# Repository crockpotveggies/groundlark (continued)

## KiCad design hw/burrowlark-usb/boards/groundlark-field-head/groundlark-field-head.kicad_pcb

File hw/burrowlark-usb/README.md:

# Burrowlark USB — DAQUSB-01

Burrowlark is the separate 70 × 45 mm USB-C magnetometer and enclosure-climate
sensor head. It uses the PNI 14190 RM3100 XYZ module; U3/C5 and their pressure-sensor
branches are removed. The DLVR pressure sensor is on DAQHAT-01. Prototype
[USB-head firmware](../../sw/field-head/README.md) has native and ARM checks;
physical qualification remains pending.

Native PCB render with the Groundlark favicon, Burrowlark name and
`DAQUSB-01 / REV A2` front silkscreen. The existing A2 board revision is retained.
Module, fuse and SHT45 bodies are simplified envelopes; see
[render provenance](boards/groundlark-field-head/render-provenance.json).

- [Electrical source](elec/field_head.ato)
- [Placement inputs](layout/placement.json)
- [Routed KiCad project](boards/groundlark-field-head/groundlark-field-head.kicad_pro)
- [Assembly and interface guide](../../docs/usb-sensor-head.md)
- [Firmware directory](../../sw/field-head/)

Build target: `field_head` in [hw/ato.yaml](../ato.yaml). Existing CAD filenames
and the DAQUSB-01 model identifier are preserved.

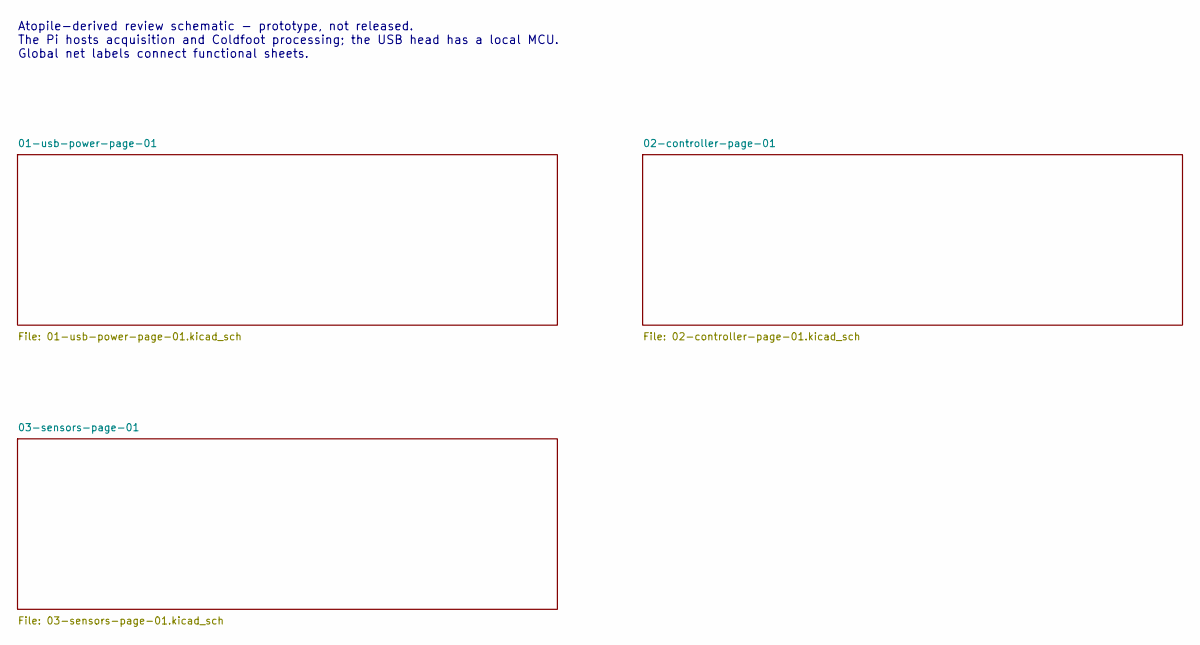
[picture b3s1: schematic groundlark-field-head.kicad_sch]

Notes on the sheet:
Atopile-derived review schematic - prototype, not released. The Pi hosts acquisition and Coldfoot processing; the USB head has a local MCU. Global net labels connect functional sheets.

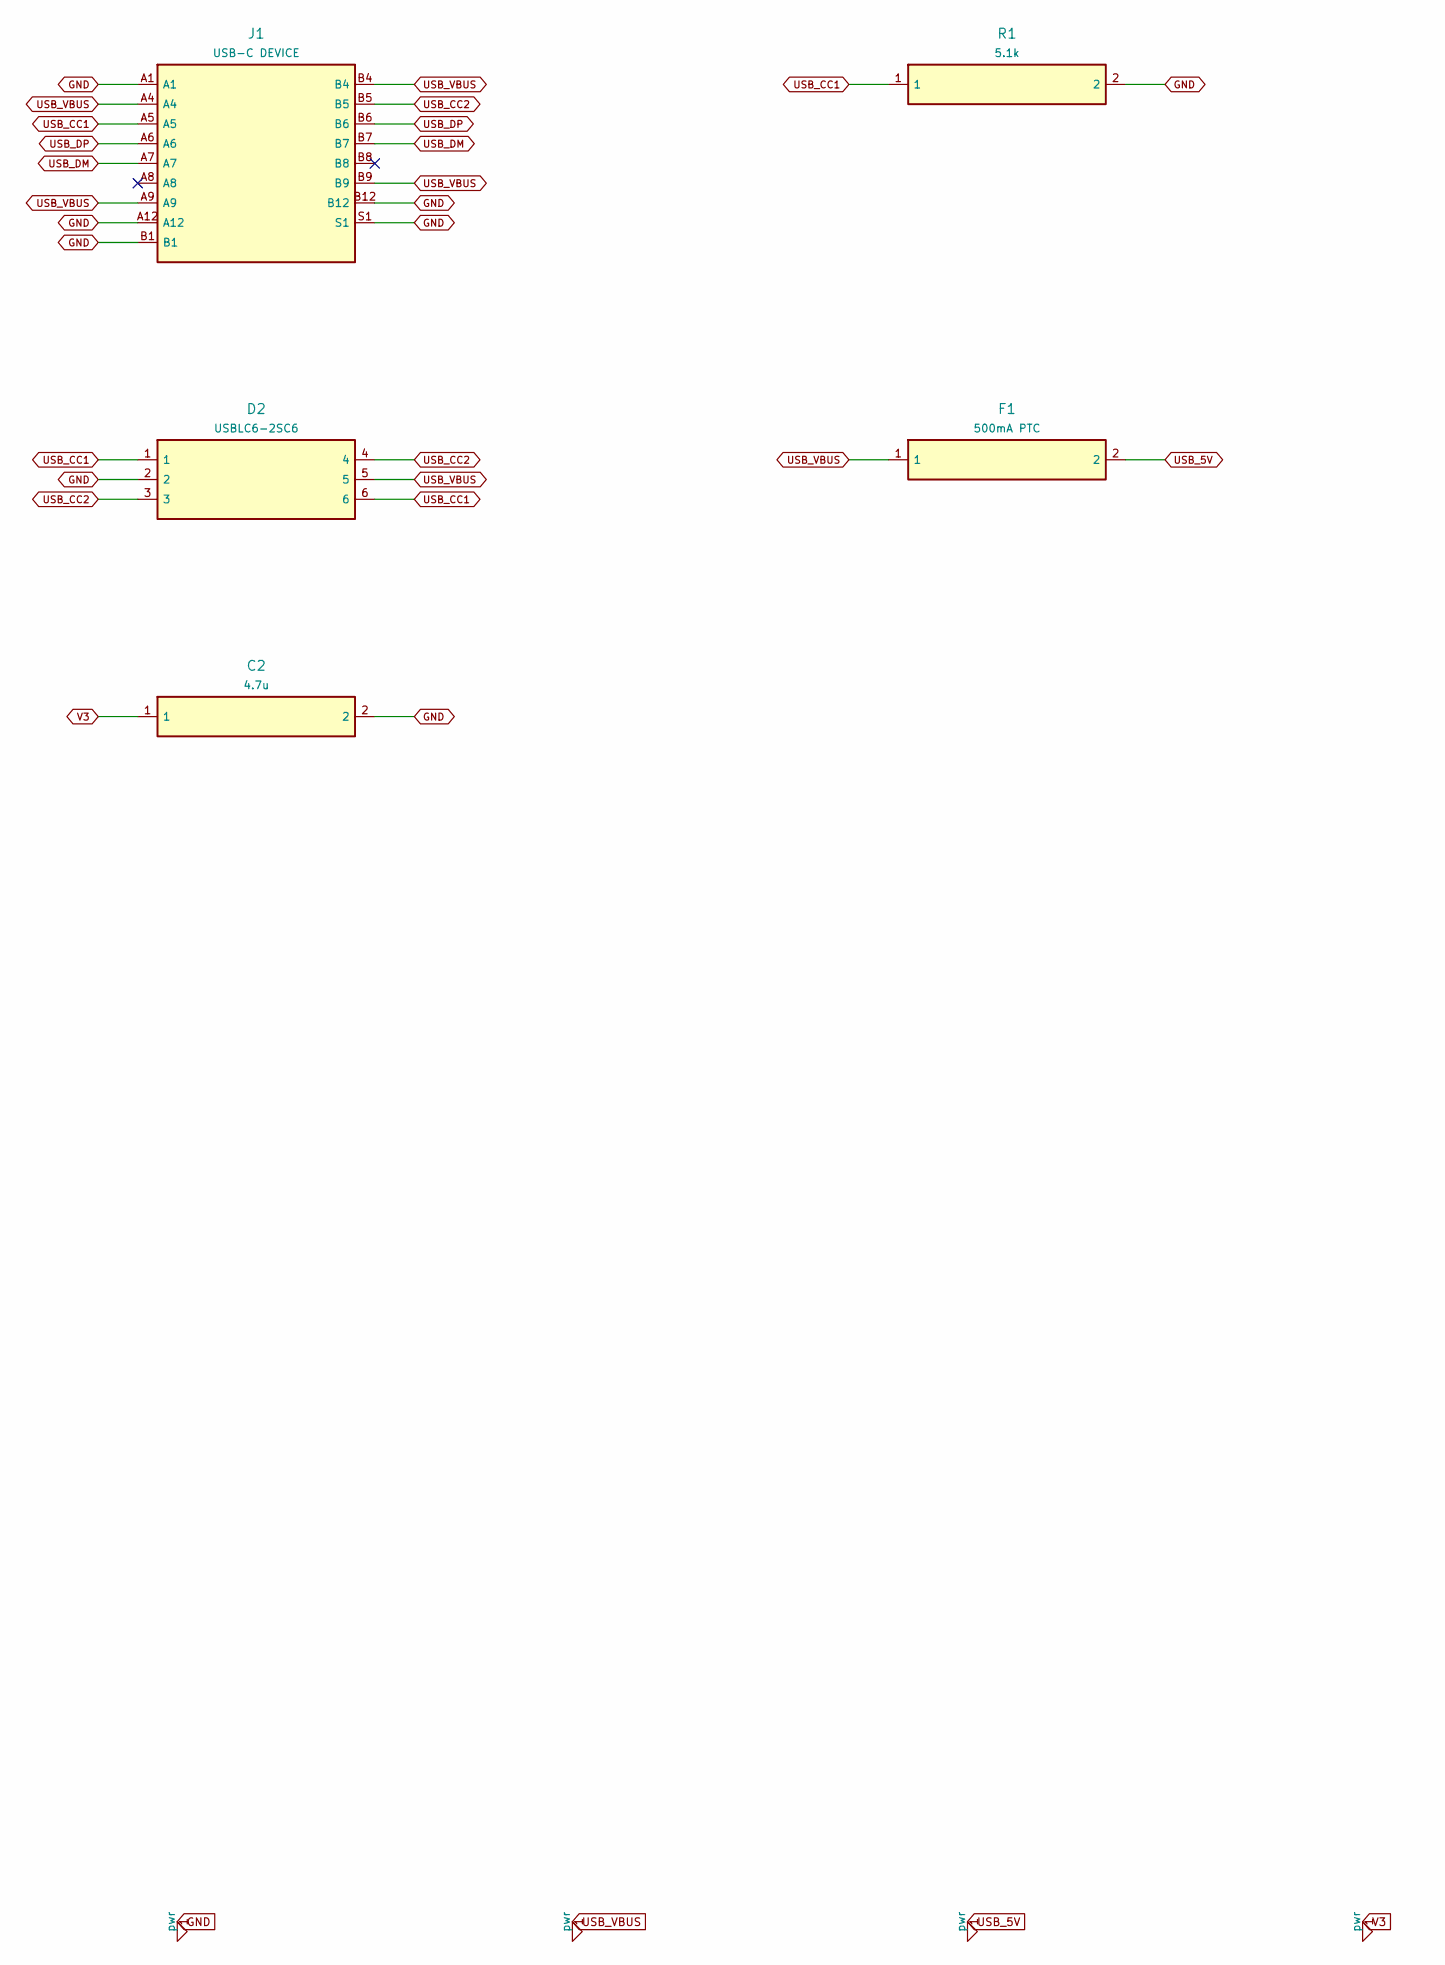
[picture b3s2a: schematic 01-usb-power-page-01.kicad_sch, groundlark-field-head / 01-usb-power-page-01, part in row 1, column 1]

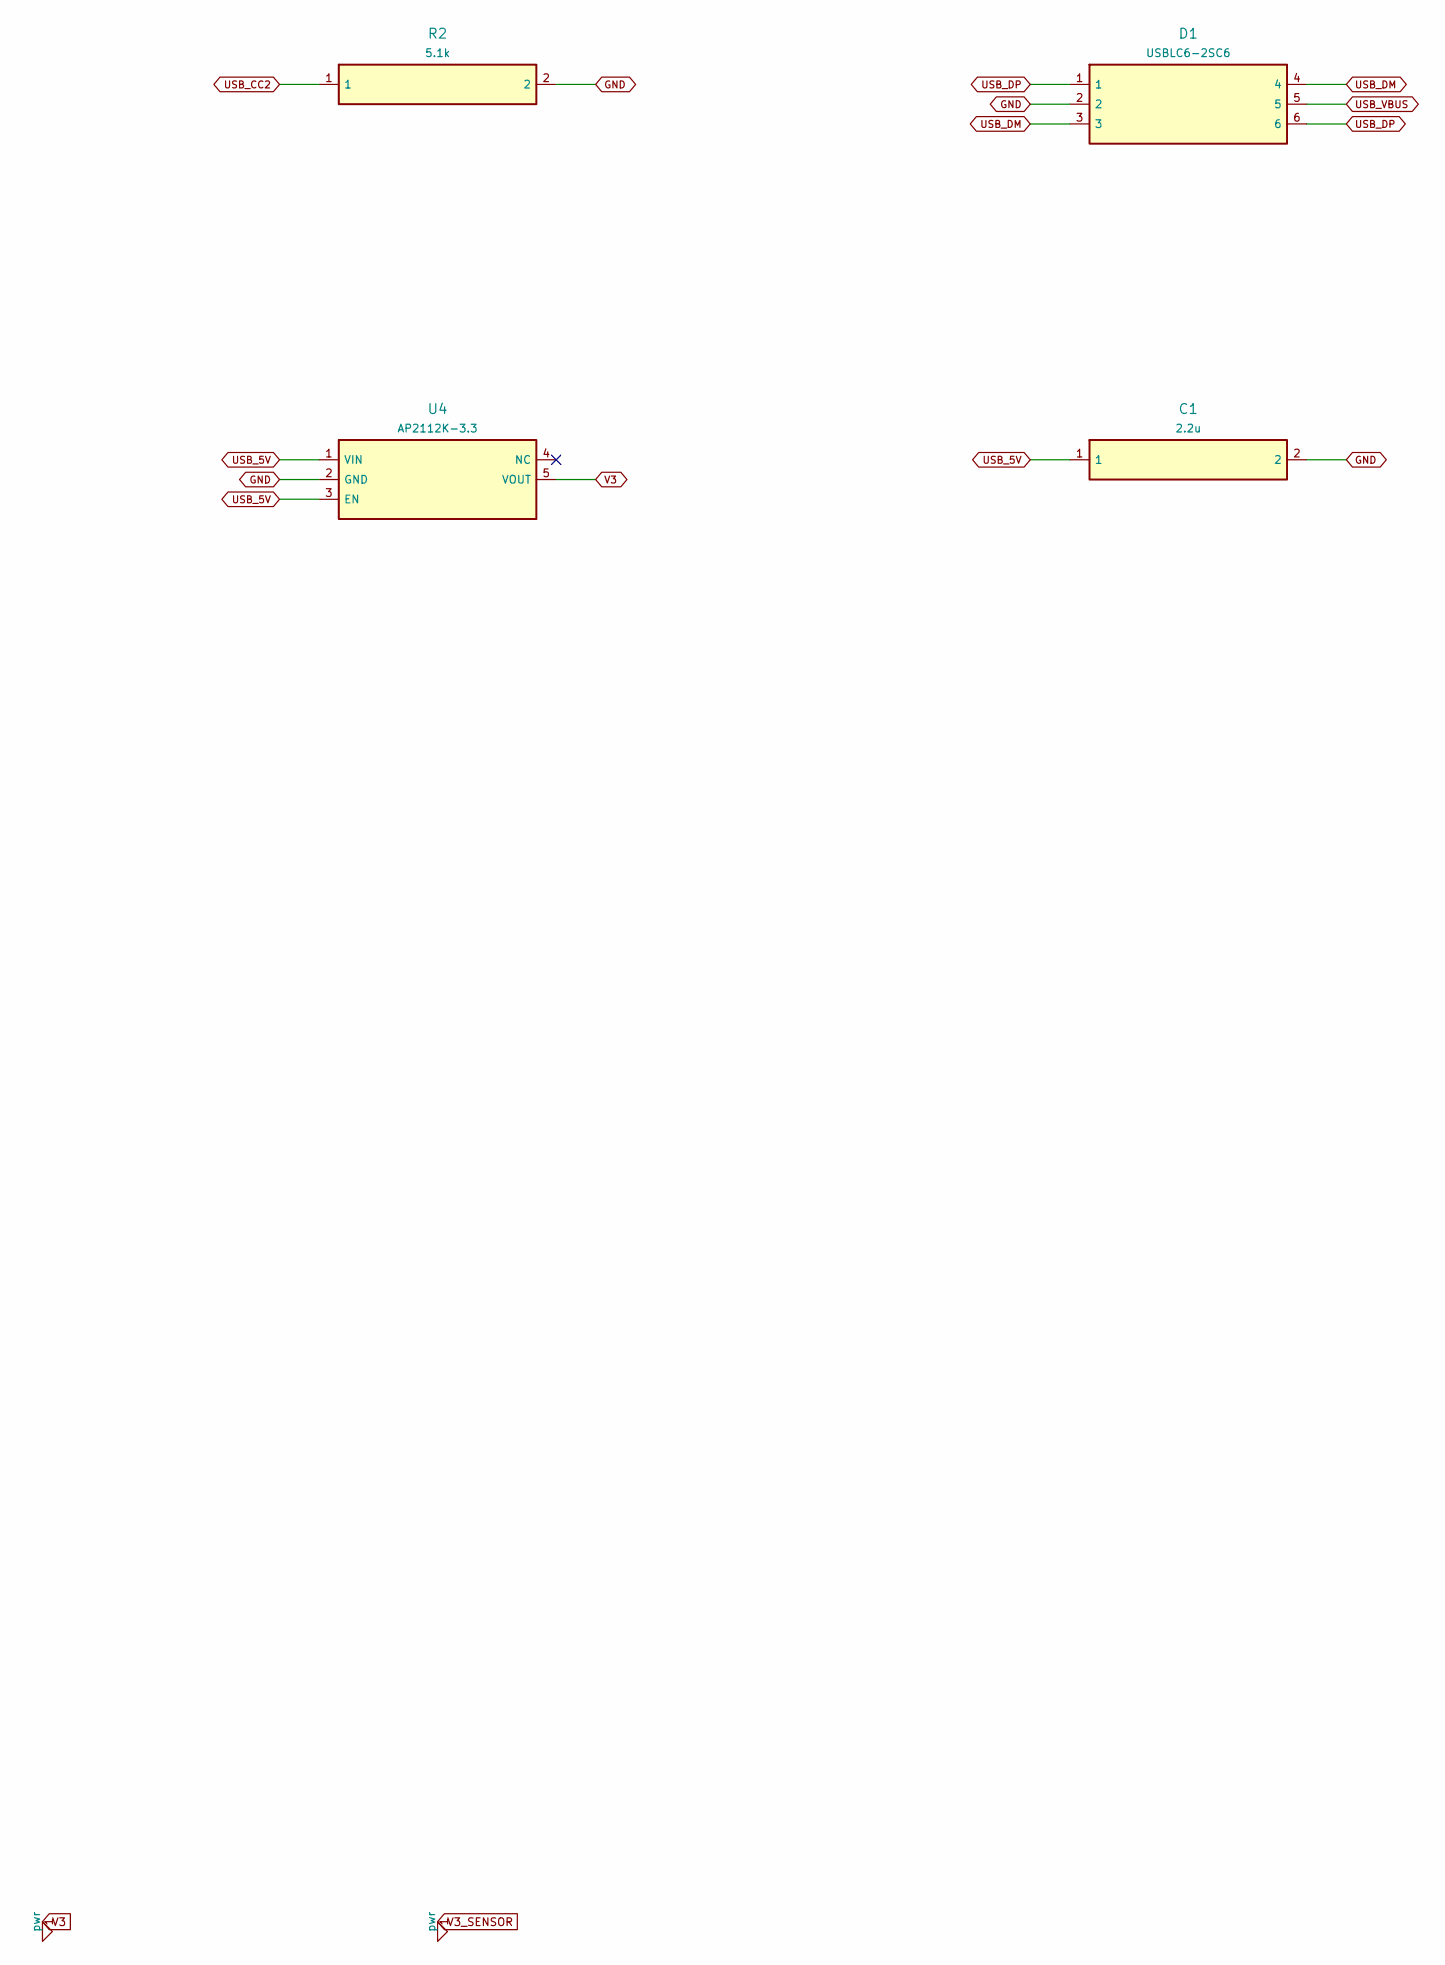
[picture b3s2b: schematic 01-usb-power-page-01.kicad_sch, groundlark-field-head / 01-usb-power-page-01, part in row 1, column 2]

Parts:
C1: 2.2u; Capacitor_SMD__C_0805_2012Metric; MPN GRM21BR71E225KA73L
C2: 4.7u; Capacitor_SMD__C_0805_2012Metric; MPN GRM21BR71A475KA73L
D1, D2: USBLC6-2SC6; Package_TO_SOT_SMD__SOT-23-6; MPN USBLC6-2SC6
F1: 500mA PTC; Fuse__Fuse_1812_4532Metric; MPN MF-MSMF050-2
J1: USB-C DEVICE; Connector_USB__USB_C_Receptacle_GCT_USB4105-xx-A_16P_TopMnt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; MPN USB4105-GF-A
R1, R2: 5.1k; Resistor_SMD__R_0603_1608Metric; MPN RC0603FR-075K1L
U4: AP2112K-3.3; Package_TO_SOT_SMD__SOT-23-5; MPN AP2112K-3.3TRG1

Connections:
4: U4.4 (NC)
A8: J1.A8
B8: J1.B8
GND: C1.2, C2.2, D1.2, D2.2, J1.A1, J1.A12, J1.B1, J1.B12, J1.S1, R1.2, R2.2, U4.2 (GND); also elsewhere on the board
USB_5V: C1.1, F1.2, U4.1 (VIN), U4.3 (EN)
USB_CC1: D2.1, D2.6, J1.A5, R1.1
USB_CC2: D2.3, D2.4, J1.B5, R2.1
USB_DM: D1.3, D1.4, J1.A7, J1.B7; also elsewhere on the board
USB_DP: D1.1, D1.6, J1.A6, J1.B6; also elsewhere on the board
USB_VBUS: D1.5, D2.5, F1.1, J1.A4, J1.A9, J1.B4, J1.B9
V3: C2.1, U4.5 (VOUT); also elsewhere on the board

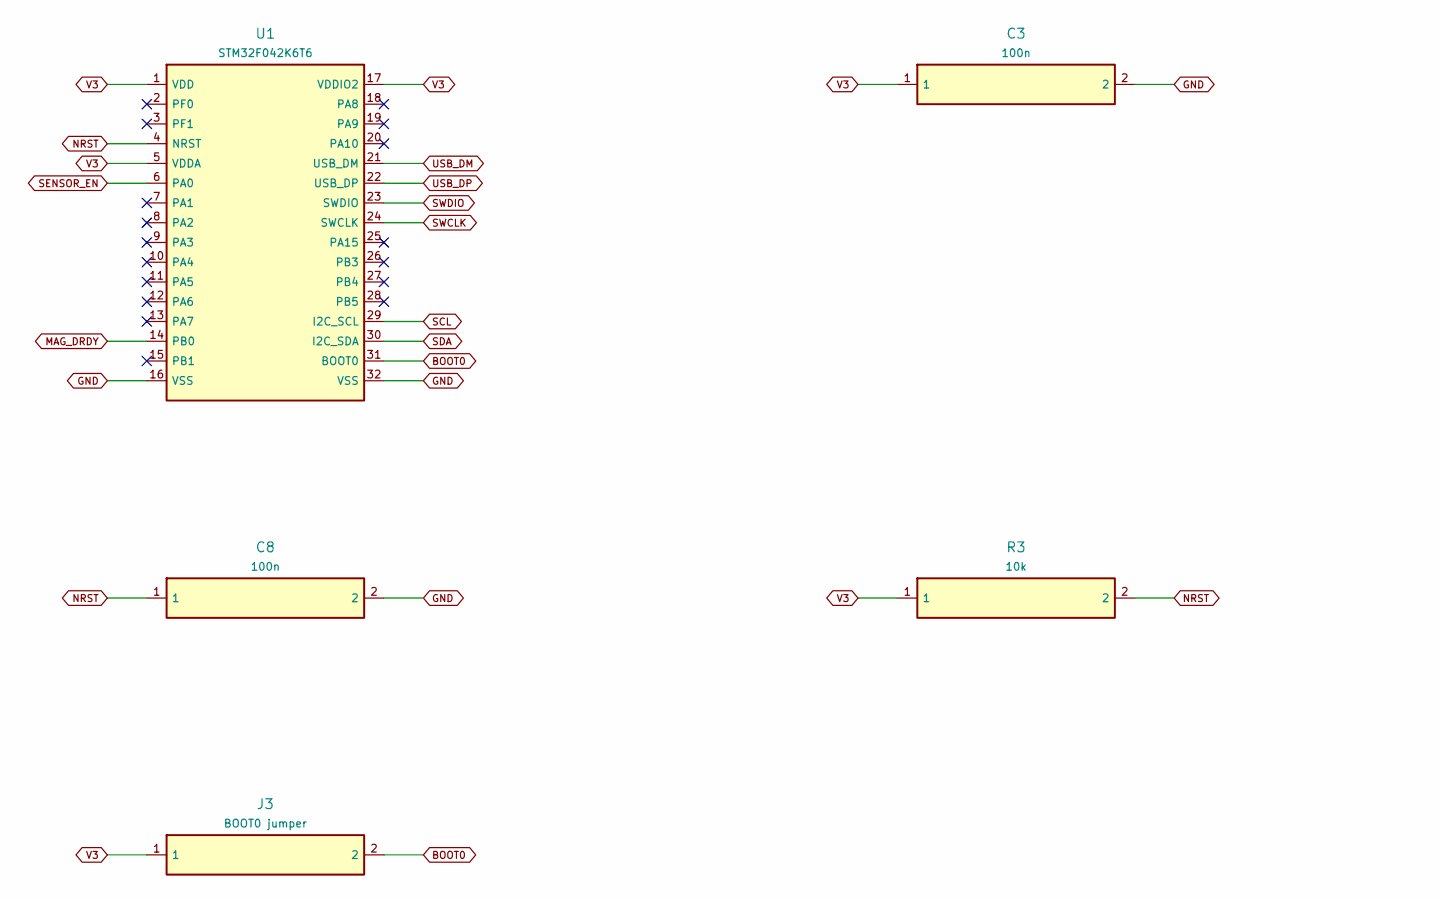
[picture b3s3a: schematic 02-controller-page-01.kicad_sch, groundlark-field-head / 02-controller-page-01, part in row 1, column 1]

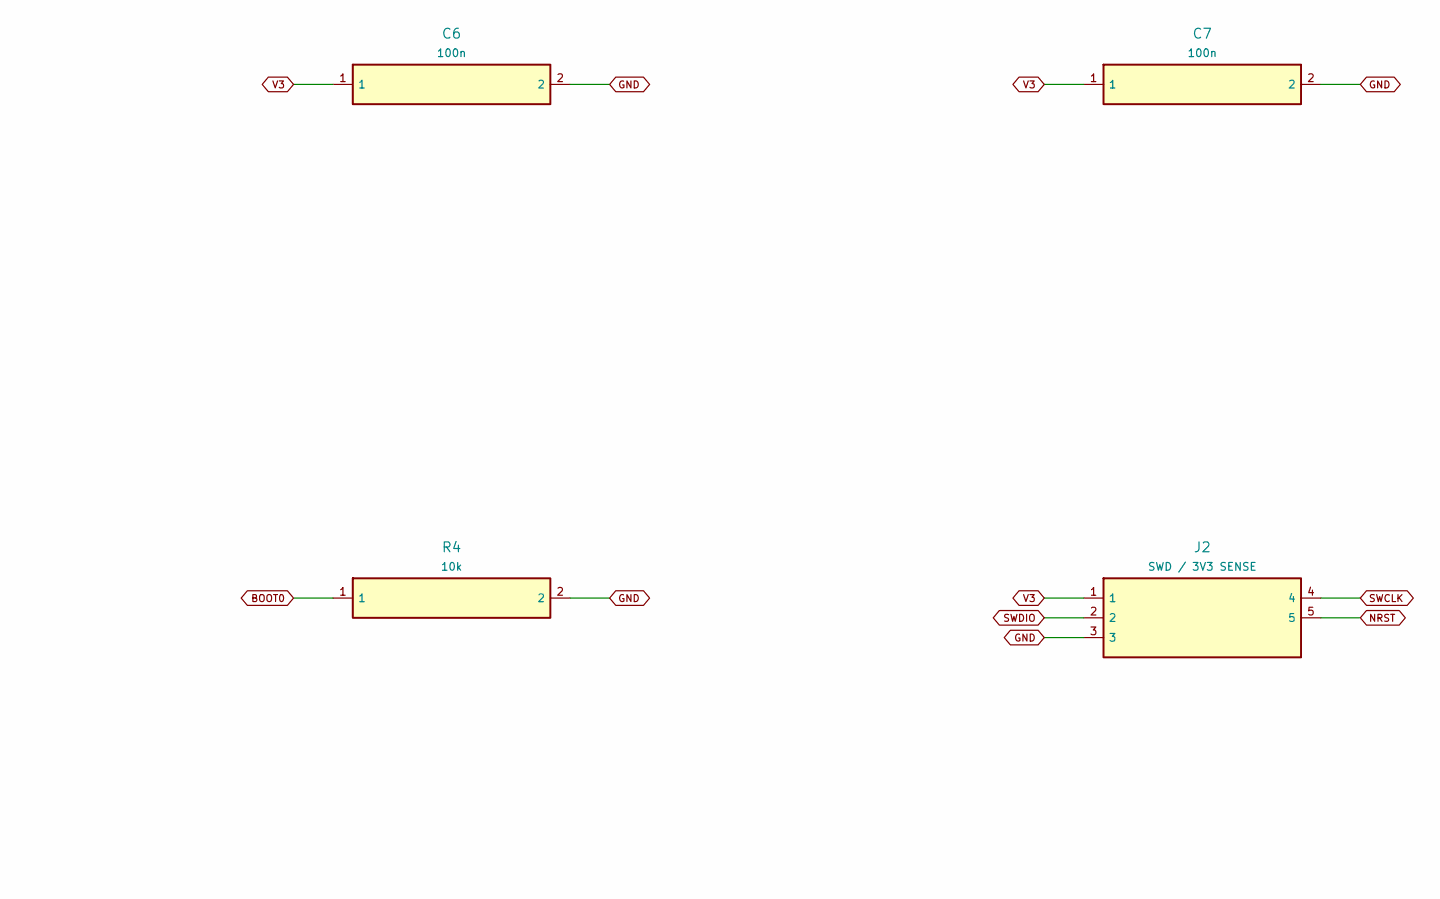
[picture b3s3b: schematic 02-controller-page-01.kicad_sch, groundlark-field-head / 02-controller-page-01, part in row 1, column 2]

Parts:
C3, C6, C7, C8: 100n; Capacitor_SMD__C_0603_1608Metric; MPN GRM188R71H104KA93D
J2: SWD / 3V3 SENSE; Connector_PinHeader_2.54mm__PinHeader_1x05_P2.54mm_Vertical; MPN M20-9990545
J3: BOOT0 jumper; Connector_PinHeader_2.54mm__PinHeader_1x02_P2.54mm_Vertical; MPN EEPROM write enable
R3, R4: 10k; Resistor_SMD__R_0603_1608Metric; MPN RC0603FR-0710KL
U1: STM32F042K6T6; Package_QFP__LQFP-32_7x7mm_P0.8mm; MPN STM32F042K6T6

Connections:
2: U1.2 (PF0)
3: U1.3 (PF1)
7: U1.7 (PA1)
8: U1.8 (PA2)
9: U1.9 (PA3)
10: U1.10 (PA4)
11: U1.11 (PA5)
12: U1.12 (PA6)
13: U1.13 (PA7)
15: U1.15 (PB1)
18: U1.18 (PA8)
19: U1.19 (PA9)
20: U1.20 (PA10)
25: U1.25 (PA15)
26: U1.26 (PB3)
27: U1.27 (PB4)
28: U1.28 (PB5)
BOOT0: J3.2, R4.1, U1.31 (BOOT0)
GND: C3.2, C6.2, C7.2, C8.2, J2.3, R4.2, U1.16 (VSS), U1.32 (VSS); also elsewhere on the board
MAG_DRDY: U1.14 (PB0); also elsewhere on the board
NRST: C8.1, J2.5, R3.2, U1.4 (NRST)
SCL: U1.29 (I2C_SCL); also elsewhere on the board
SDA: U1.30 (I2C_SDA); also elsewhere on the board
SENSOR_EN: U1.6 (PA0); also elsewhere on the board
SWCLK: J2.4, U1.24 (SWCLK)
SWDIO: J2.2, U1.23 (SWDIO)
USB_DM: U1.21 (USB_DM); also elsewhere on the board
USB_DP: U1.22 (USB_DP); also elsewhere on the board
V3: C3.1, C6.1, C7.1, J2.1, J3.1, R3.1, U1.1 (VDD), U1.5 (VDDA), U1.17 (VDDIO2); also elsewhere on the board

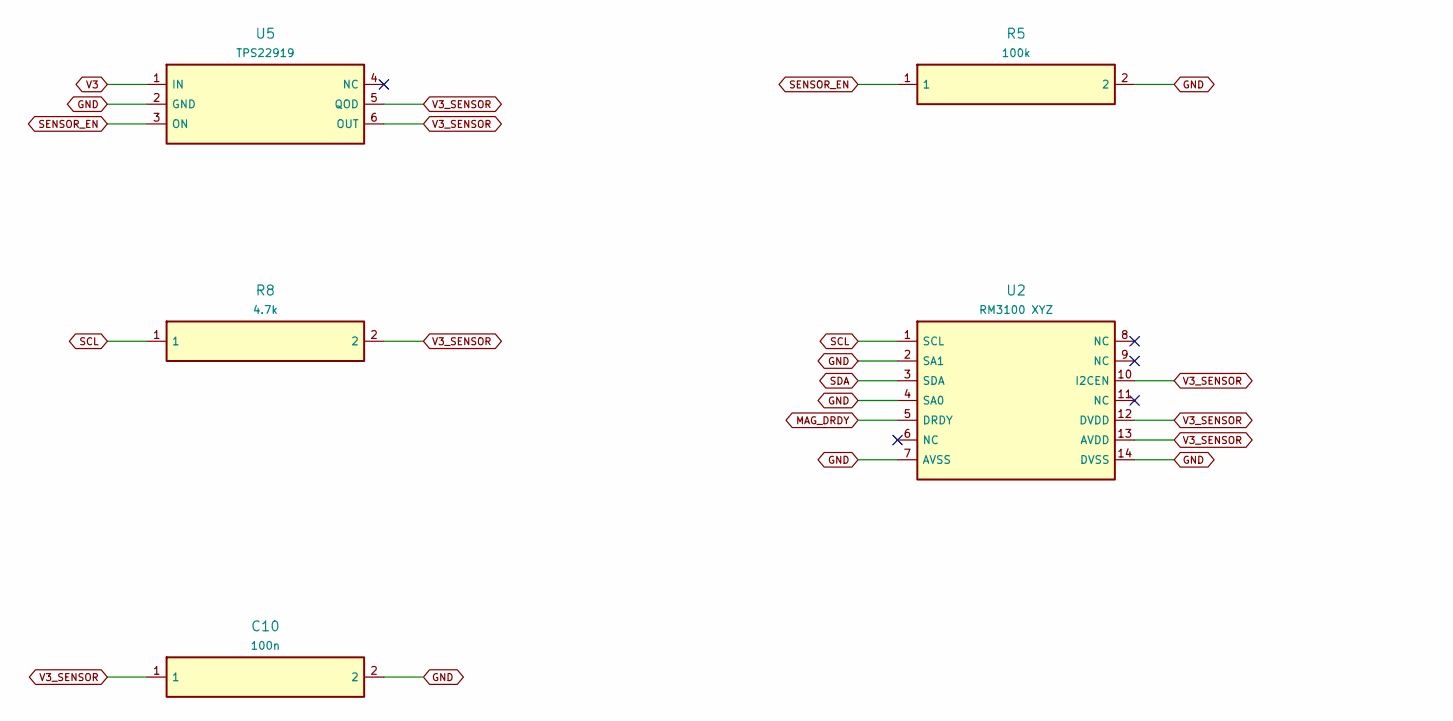
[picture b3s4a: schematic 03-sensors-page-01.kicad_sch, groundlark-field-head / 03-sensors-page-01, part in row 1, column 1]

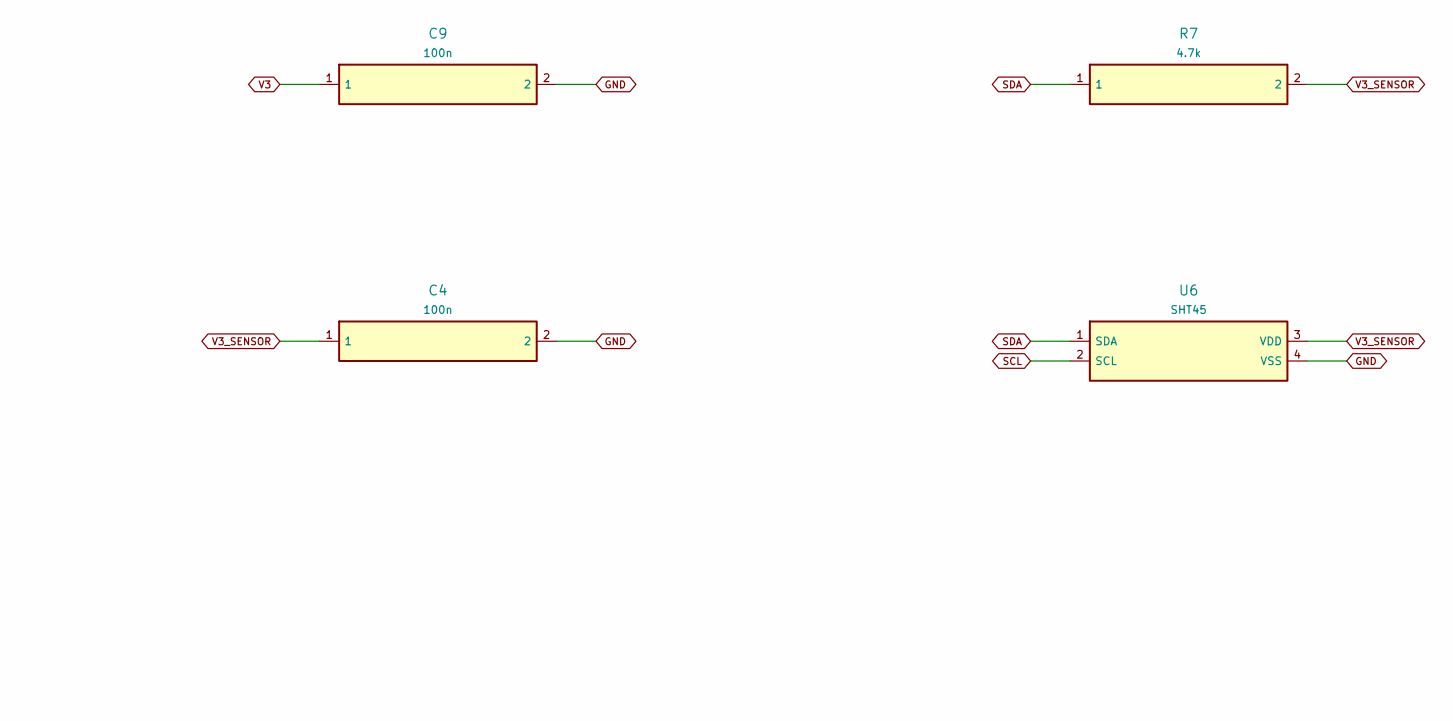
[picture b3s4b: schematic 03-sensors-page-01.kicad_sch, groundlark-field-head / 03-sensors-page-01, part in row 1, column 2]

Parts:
C4, C9, C10: 100n; Capacitor_SMD__C_0603_1608Metric; MPN GRM188R71H104KA93D
R5: 100k; Resistor_SMD__R_0603_1608Metric; MPN RC0603FR-07100KL
R7, R8: 4.7k; Resistor_SMD__R_0603_1608Metric; MPN RC0603FR-074K7L
U2: RM3100 XYZ; Groundlark__PNI_14190_Module; MPN PNI 14190
U5: TPS22919; Package_TO_SOT_SMD__SOT-363_SC-70-6; MPN TPS22919DCKR
U6: SHT45; MPN SHT45-AD1B-R2

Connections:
6: U2.6 (NC)
GND: C4.2, C9.2, C10.2, R5.2, U2.2 (SA1), U2.4 (SA0), U2.7 (AVSS), U2.14 (DVSS), U5.2 (GND), U6.4 (VSS); also elsewhere on the board
MAG_DRDY: U2.5 (DRDY); also elsewhere on the board
SCL: R8.1, U2.1 (SCL), U6.2 (SCL); also elsewhere on the board
SDA: R7.1, U2.3 (SDA), U6.1 (SDA); also elsewhere on the board
SENSOR_EN: R5.1, U5.3 (ON); also elsewhere on the board
V3: C9.1, U5.1 (IN); also elsewhere on the board
V3_SENSOR: C4.1, C10.1, R7.2, R8.2, U2.10 (I2CEN), U2.12 (DVDD), U2.13 (AVDD), U5.5 (QOD), U5.6 (OUT), U6.3 (VDD)
u2-8: U2.8 (NC)
u2-9: U2.9 (NC)
u2-11: U2.11 (NC)
u5-4: U5.4 (NC)

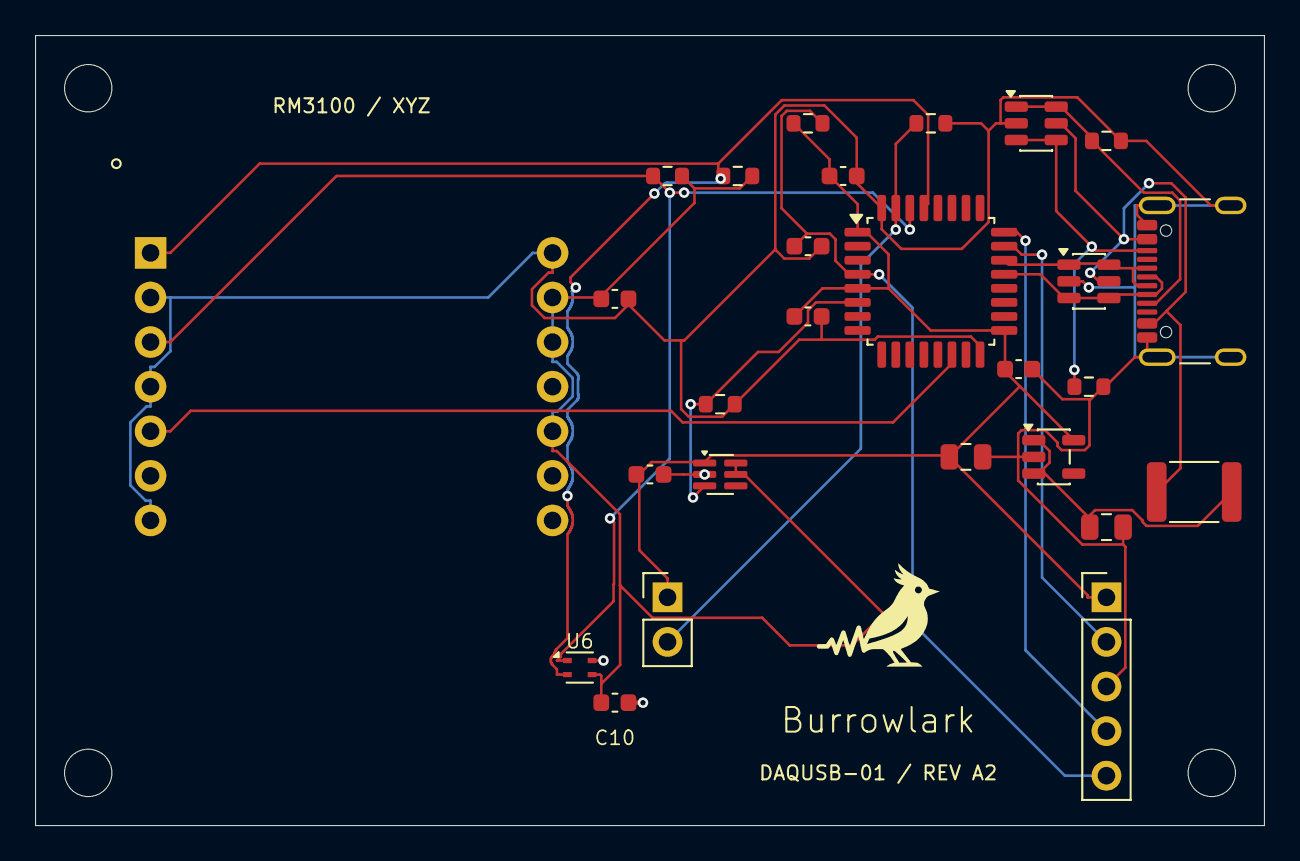
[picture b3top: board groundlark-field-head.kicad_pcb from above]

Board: 4 copper layers, 70.0 x 45.0 mm, 31 parts (0 on the bottom side), 17 nets.

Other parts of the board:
H1, H2, H3, H4: M2.5 NPTH; MountingHole__MountingHole_2.7mm_M2.5

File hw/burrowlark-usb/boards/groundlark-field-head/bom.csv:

Reference,Value,MPN,Footprint,DNP,Note
J1,USB-C DEVICE,USB4105-GF-A,Connector_USB__USB_C_Receptacle_GCT_USB4105-xx-A_16P_TopMnt_Horizontal,False,
R1,5.1k,RC0603FR-075K1L,Resistor_SMD__R_0603_1608Metric,False,
R2,5.1k,RC0603FR-075K1L,Resistor_SMD__R_0603_1608Metric,False,
D1,USBLC6-2SC6,USBLC6-2SC6,Package_TO_SOT_SMD__SOT-23-6,False,
D2,USBLC6-2SC6,USBLC6-2SC6,Package_TO_SOT_SMD__SOT-23-6,False,
F1,500mA PTC,MF-MSMF050-2,Fuse__Fuse_1812_4532Metric,False,
U4,AP2112K-3.3,AP2112K-3.3TRG1,Package_TO_SOT_SMD__SOT-23-5,False,
C1,2.2u,GRM21BR71E225KA73L,Capacitor_SMD__C_0805_2012Metric,False,
C2,4.7u,GRM21BR71A475KA73L,Capacitor_SMD__C_0805_2012Metric,False,
U1,STM32F042K6T6,STM32F042K6T6,Package_QFP__LQFP-32_7x7mm_P0.8mm,False,
C3,100n,GRM188R71H104KA93D,Capacitor_SMD__C_0603_1608Metric,False,
C6,100n,GRM188R71H104KA93D,Capacitor_SMD__C_0603_1608Metric,False,
C7,100n,GRM188R71H104KA93D,Capacitor_SMD__C_0603_1608Metric,False,
C8,100n,GRM188R71H104KA93D,Capacitor_SMD__C_0603_1608Metric,False,
R3,10k,RC0603FR-0710KL,Resistor_SMD__R_0603_1608Metric,False,
R4,10k,RC0603FR-0710KL,Resistor_SMD__R_0603_1608Metric,False,
J2,SWD / 3V3 SENSE,M20-9990545,Connector_PinHeader_2.54mm__PinHeader_1x05_P2.54mm_Vertical,False,Pin 1 is target voltage sense; do not externally power the rail
J3,BOOT0 jumper,EEPROM write enable,Connector_PinHeader_2.54mm__PinHeader_1x02_P2.54mm_Vertical,False,
U5,TPS22919,TPS22919DCKR,Package_TO_SOT_SMD__SOT-363_SC-70-6,False,
R5,100k,RC0603FR-07100KL,Resistor_SMD__R_0603_1608Metric,False,
C9,100n,GRM188R71H104KA93D,Capacitor_SMD__C_0603_1608Metric,False,
R7,4.7k,RC0603FR-074K7L,Resistor_SMD__R_0603_1608Metric,False,
R8,4.7k,RC0603FR-074K7L,Resistor_SMD__R_0603_1608Metric,False,
U2,RM3100 XYZ,PNI 14190,Groundlark__PNI_14190_Module,False,
C4,100n,GRM188R71H104KA93D,Capacitor_SMD__C_0603_1608Metric,False,
H1,M2.5 NPTH,M2.5 NPTH,MountingHole__MountingHole_2.7mm_M2.5,False,
H2,M2.5 NPTH,M2.5 NPTH,MountingHole__MountingHole_2.7mm_M2.5,False,
H3,M2.5 NPTH,M2.5 NPTH,MountingHole__MountingHole_2.7mm_M2.5,False,
H4,M2.5 NPTH,M2.5 NPTH,MountingHole__MountingHole_2.7mm_M2.5,False,
U6,SHT45,SHT45-AD1B-R2,SHT45,False,Enclosure temperature/humidity; 0x44; heater disabled; keep sensing opening exposed
C10,100n,GRM188R71H104KA93D,Capacitor_SMD__C_0603_1608Metric,False,SHT45 local bypass

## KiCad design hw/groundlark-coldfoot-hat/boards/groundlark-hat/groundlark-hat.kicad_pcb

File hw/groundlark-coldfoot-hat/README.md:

# Groundlark Coldfoot HAT

The 120 × 56 mm A2 ASIC HAT is retained as a separate hardware design.
Coldfoot ASIC/runtime/RTL integration is deferred while work focuses on the
Groundlark FPGA HAT. Existing CAD is prototype material, not a fabrication release.

- [Electrical source](elec/hat.ato)
- [Placement inputs](layout/placement.json)
- [Fixed connector routing](layout/fixed-routes.json)
- [Routed KiCad project](boards/groundlark-hat/groundlark-hat.kicad_pro)
- [Design specifications](../../docs/design-a0.md)
- [Coldfoot integration](../../docs/coldfoot-integration.md)

Build target: `hat` in [hw/ato.yaml](../ato.yaml). Vendor attribution and reference
boards remain in [shared/vendor/wafer-space/](../shared/vendor/wafer-space/).

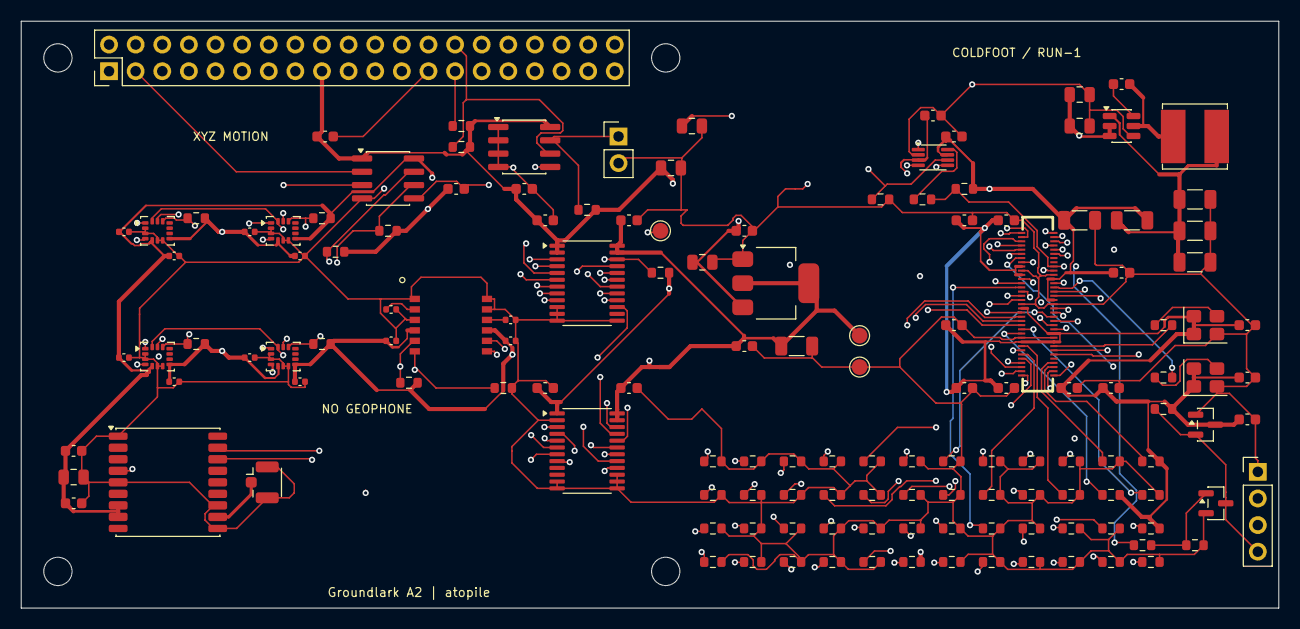
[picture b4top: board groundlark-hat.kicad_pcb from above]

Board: 6 copper layers, 120.0 x 56.0 mm, 147 parts (0 on the bottom side), 106 nets.

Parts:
C1, C24, C26, C41, C43, C44, C45, C46, C47, C48, C49, C62, C67, C68, C69, C70, C71, C72, C73, C74, C75, C76, C77, C78, C79: 100n; Capacitor_SMD__C_0603_1608Metric
C2, C3, C40, C60, C61: 10u; Capacitor_SMD__C_0805_2012Metric
C12, C13, C14, C15, C16, C17, C18, C19, C20, C21, C22, C23: 100n; Capacitor_SMD__C_0402_1005Metric
C25: 4.7u; Capacitor_SMD__C_0805_2012Metric
C42, C63, C64, C65, C66: 22u; Capacitor_SMD__C_1206_3216Metric
H1, H2, H3, H4: M2.5 NPTH; MountingHole__MountingHole_2.7mm_M2.5
J1: Raspberry Pi 40-pin; Connector_PinHeader_2.54mm__PinHeader_2x20_P2.54mm_Vertical
J2: Passive GNSS antenna; Connector_Coaxial__U.FL_Hirose_U.FL-R-SMT-1_Vertical
J4: Coldfoot test UART/reset; Connector_PinHeader_2.54mm__PinHeader_1x04_P2.54mm_Vertical
J5: Coldfoot run-1 1x1; Coldfoot_Run1_70DS
JP1: EEPROM write enable; Connector_PinHeader_2.54mm__PinHeader_1x02_P2.54mm_Vertical
L1: 4.7uH; Inductor_SMD__L_Bourns_SRN6045TA
Q1: 2N7002; Package_TO_SOT_SMD__SOT-23
R1, R2: 3.9k; Resistor_SMD__R_0603_1608Metric
R3, R65: 1k; Resistor_SMD__R_0603_1608Metric
R11, R12, R13, R14, R20, R50, R63, R64: 10k; Resistor_SMD__R_0603_1608Metric
R51, R62, R66, R100, R101, R102, R103, R104, R105, R106, R107, R108, R109, R110, R111, R112, R113, R114, R115, R116, R117, R118, R119, R120, R121, R122, R123, R124, R125, R126, R127, R128, R129, R130, R131, R132, R133, R134, R135, R136, R137, R138, R139, R140, R141, R142, R143, R144, R145, R146, R147: 100k; Resistor_SMD__R_0603_1608Metric
R52, R53: 4.7k; Resistor_SMD__R_0603_1608Metric
R60: 0.1; Resistor_SMD__R_1206_3216Metric
R61: 47; Resistor_SMD__R_0603_1608Metric
R67, R68: 33; Resistor_SMD__R_0603_1608Metric
TP1: SENS_3V3; TestPoint__TestPoint_Pad_D1.5mm
TP2: GND; TestPoint__TestPoint_Pad_D1.5mm
TP4: SENSOR_OE_N; TestPoint__TestPoint_Pad_D1.5mm
U1: 24LC32A; Package_SO__SOIC-8_3.9x4.9mm_P1.27mm
U11, U12, U13, U14: LSM6DSOTR; Package_LGA__LGA-14_3x2.5mm_P0.5mm_LayoutBorder3x4y
U20: SCL3300-D01; Groundlark__SCL3300_D01
U21: MAX-M10S; RF_GPS__ublox_MAX
U40: TLV1117LV33DCYR; Package_TO_SOT_SMD__SOT-223-3_TabPin2
U41, U42: SN74LVC8T245PWR; Package_SO__TSSOP-24_4.4x7.8mm_P0.65mm
U43: ISO1640BDR; Package_SO__SOIC-8_3.9x4.9mm_P1.27mm
U50: AP63203WU-7; Package_TO_SOT_SMD__TSOT-23-6
U51: TXU0202DCUR; Package_SO__VSSOP-8_2.3x2mm_P0.5mm
U52: TLV803EA30DBZR; Package_TO_SOT_SMD__SOT-23
Y1, Y2: 25MHz; Crystal__Crystal_SMD_3225-4Pin_3.2x2.5mm

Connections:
CF_3V3: C66.1, C67.1, C68.1, C69.1, C70.1, C71.1, C72.1, C73.1, C74.1, C76.1, C77.1, C78.1, C79.1, J5.9, J5.11, J5.19, J5.24, J5.44, J5.46, J5.54, J5.62, R60.2, R63.2, R64.2, R111.2, R122.2, R135.2, R141.2, U51.7, U52.3, Y1.1, Y1.4, Y2.1, Y2.4
CF_BIDIR_2: J5.4, R110.1
CF_BIDIR_3: J5.3, R111.1
CF_BIDIR_4: J5.2, R112.1
CF_BIDIR_5: J5.1, R113.1
CF_BIDIR_6: J5.70, R114.1
CF_BIDIR_7: J5.69, R115.1
CF_BIDIR_8: J5.68, R116.1
CF_BIDIR_9: J5.67, R117.1
CF_BIDIR_10: J5.66, R118.1
CF_BIDIR_11: J5.65, R119.1
CF_BIDIR_12: J5.64, R120.1
CF_BIDIR_13: J5.63, R121.1
CF_BIDIR_14: J5.60, R122.1
CF_BIDIR_15: J5.59, R123.1
CF_BIDIR_16: J5.58, R124.1
CF_BIDIR_17: J5.57, R125.1
CF_BIDIR_18: J5.56, R126.1
CF_BIDIR_19: J5.55, R127.1
CF_BIDIR_20: J5.52, R128.1
CF_BIDIR_21: J5.51, R129.1
CF_BIDIR_22: J5.50, R130.1
CF_BIDIR_23: J5.49, R131.1
CF_BIDIR_24: J5.48, R132.1
CF_BIDIR_25: J5.47, R133.1
CF_BIDIR_26: J5.43, R134.1
CF_BIDIR_27: J5.42, R135.1
CF_BIDIR_28: J5.41, R136.1
CF_BIDIR_29: J5.40, R137.1
CF_BIDIR_30: J5.39, R138.1
CF_BIDIR_31: J5.38, R139.1
CF_BIDIR_32: J5.37, R140.1
CF_BIDIR_33: J5.36, R141.1
CF_BIDIR_34: J5.35, R142.1
CF_BIDIR_35: J5.34, R143.1
CF_BIDIR_36: J5.33, R144.1
CF_BIDIR_37: J5.32, R145.1
CF_BIDIR_38: J5.31, R146.1
CF_BIDIR_39: J5.30, R147.1
CF_BST: C62.1, U50.6
CF_IN_1: J5.26, R100.1
CF_IN_2: J5.23, R101.1
CF_IN_4: J5.21, R102.1
CF_IN_5: J5.20, R103.1
CF_IN_6: J5.17, R104.1
CF_IN_7: J5.16, R105.1
CF_IN_8: J5.15, R106.1
CF_IN_9: J5.14, R107.1
CF_IN_10: J5.13, R108.1
CF_IN_11: J5.12, R109.1
CF_IO_ENABLE: J1.22, R62.1, U51.6
CF_MESH_CLK: J5.8, R67.2
CF_MESH_CLK_RAW: R67.1, Y1.3
CF_REG_3V3: C63.1, C64.1, C65.1, L1.2, R60.1, U50.1
CF_RESET_GATE: Q1.1, R65.2, R66.1
CF_RESET_GPIO: J1.11, R65.1
CF_RESET_N: J4.4, J5.7, Q1.3, R64.1, U52.2
CF_SW: C62.2, L1.1, U50.5
CF_TILE_CLK: J5.22, R68.2
CF_TILE_CLK_RAW: R68.1, Y2.3
CF_UART_DRIVE: R61.1, U51.8
CF_UART_RX: J4.2, J5.27, R61.2, R63.1
CF_UART_TX: J4.3, J5.6, U51.1
EEP_WP: JP1.1, R3.1, U1.7
GND: C1.2, C2.2, C3.2, C12.2, C13.2, C14.2, C15.2, C16.2, C17.2, C18.2, C19.2, C20.2, C21.2, C22.2, C23.2, C24.2, C25.2, C26.2, C40.2, C41.2, C42.2, C43.2, C44.2, C45.2, C46.2, C47.2, C48.2, C49.2, C60.2, C61.2, C63.2, C64.2, C65.2, C66.2, C67.2, C68.2, C69.2, C70.2, C71.2, C72.2, C73.2, C74.2, C75.2, C76.2, C77.2, C78.2, C79.2, J1.6, J1.9, J1.14, J1.20, J1.25, J1.30, J1.34, J1.39, J2.2, J4.1, J5.10, J5.18, J5.25, J5.45, J5.53, J5.61, JP1.2, Q1.2, R51.2, R62.2, R66.2, R100.2, R101.2, R102.2, R103.2, R104.2, R105.2, R106.2, R107.2, R108.2, R109.2, R110.2, R112.2, R113.2, R114.2, R115.2, R116.2, R117.2, R118.2, R119.2, R120.2, R121.2, R123.2, R124.2, R125.2, R126.2, R127.2, R128.2, R129.2, R130.2, R131.2, R132.2, R133.2, R134.2, R136.2, R137.2, R138.2, R139.2, R140.2, R142.2, R143.2, R144.2, R145.2, R146.2, R147.2, TP2.1, U1.1, U1.2, U1.3, U1.4, U11.2, U11.3, U11.6, U11.7, U12.2, U12.3, U12.6, U12.7, U13.2, U13.3, U13.6, U13.7, U14.2, U14.3, U14.6, U14.7, U20.1, U20.3, U20.11, U20.12, U21.1, U21.5, U21.10, U21.12, U40.1, U41.10, U41.11, U41.12, U41.13, U42.2, U42.11, U42.12, U42.13, U42.14, U42.15, U43.4, U43.5, U50.4, U51.2, U52.1, Y1.2, Y2.2
GNSS_PPS: U21.4, U42.16
GNSS_RF: J2.1, U21.11
I2C_SCL: R53.1, U21.17, U43.6
I2C_SDA: R52.1, U21.16, U43.7
ID_SCL: J1.28, R2.1, U1.6
ID_SDA: J1.27, R1.1, U1.5
IMU1_CS: R11.1, U11.12, U41.19
IMU1_INT: U11.4, U42.20
IMU2_CS: R12.1, U12.12, U41.18
IMU2_INT: U12.4, U42.19
IMU3_CS: R13.1, U13.12, U41.17
IMU3_INT: U13.4, U42.18
IMU4_CS: R14.1, U14.12, U41.16
IMU4_INT: U14.4, U42.17
PI_3V3: C1.1, C2.1, C44.1, C46.1, C48.1, C75.1, J1.1, J1.17, R1.2, R2.2, R3.2, R50.2, U1.8, U41.1, U41.2, U42.1, U43.1, U51.3
PI_5V: C3.1, C40.1, C41.1, C60.1, C61.1, J1.2, J1.4, U40.3, U50.2, U50.3
PI_GNSS_PPS: J1.7, U42.8
PI_I2C_SCL: J1.5, U43.3
PI_I2C_SDA: J1.3, U43.2
PI_IMU1_CS: J1.24, U41.5
PI_IMU1_INT: J1.13, U42.4
PI_IMU2_CS: J1.26, U41.6
PI_IMU2_INT: J1.15, U42.5
PI_IMU3_CS: J1.29, U41.7
PI_IMU3_INT: J1.16, U42.6
PI_IMU4_CS: J1.31, U41.8
PI_IMU4_INT: J1.18, U42.7
PI_SPI_MISO: J1.21, U42.3
PI_SPI_MOSI: J1.19, U41.3
PI_SPI_SCLK: J1.23, U41.4
PI_TILT_CS: J1.33, U41.9
PI_UART_RX: J1.10, U51.4
PI_UART_TX: J1.8, U51.5
SENSOR_OE_N: J1.37, R50.1, TP4.1, U41.22, U42.22
SENS_3V3: C12.1, C13.1, C14.1, C15.1, C16.1, C17.1, C18.1, C19.1, C20.1, C22.1, C24.1, C25.1, C26.1, C42.1, C43.1, C45.1, C47.1, C49.1, R11.2, R12.2, R13.2, R14.2, R20.2, R52.2, R53.2, TP1.1, U11.5, U11.8, U12.5, U12.8, U13.5, U13.8, U14.5, U14.8, U20.4, U20.9, U21.7, U21.8, U40.2, U41.23, U41.24, U42.23, U42.24, U43.8
SPI_MISO: R51.1, U11.1, U12.1, U13.1, U14.1, U20.6, U42.21
SPI_MOSI: U11.14, U12.14, U13.14, U14.14, U20.7, U41.21
SPI_SCLK: U11.13, U12.13, U13.13, U14.13, U20.8, U41.20
TILT_AEXT: C21.1, U20.2
TILT_CS: R20.1, U20.5, U41.15
TILT_DEXT: C23.1, U20.10
